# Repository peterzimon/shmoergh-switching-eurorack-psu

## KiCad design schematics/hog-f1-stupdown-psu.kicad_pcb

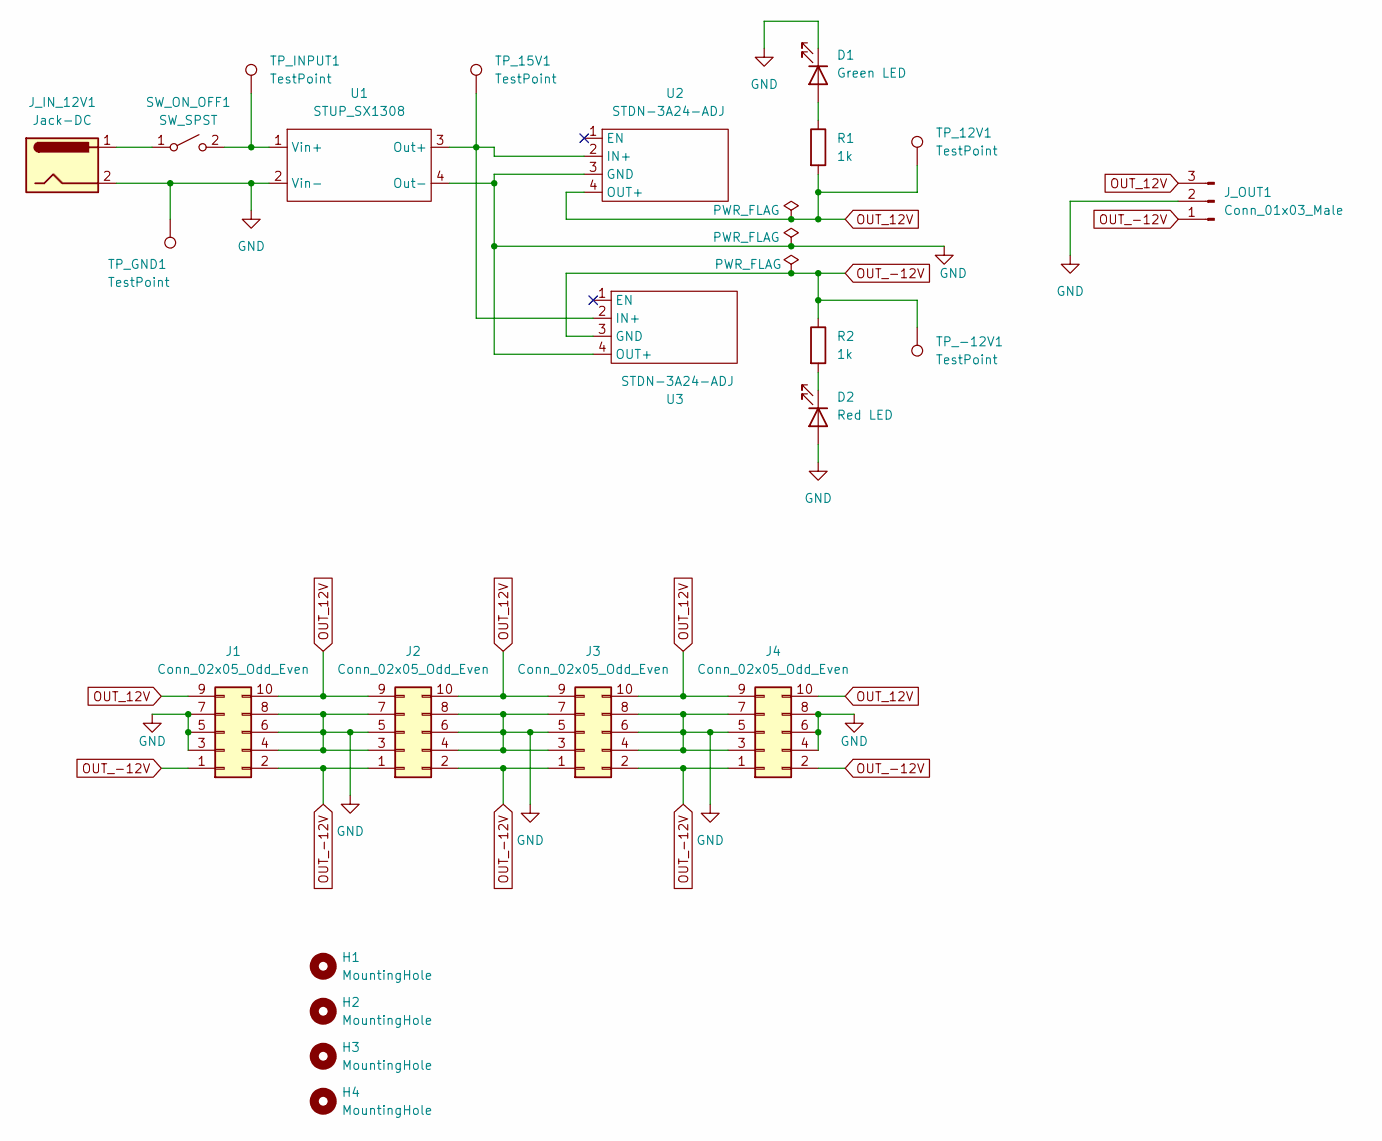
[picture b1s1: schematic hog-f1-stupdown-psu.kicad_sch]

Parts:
D1: Green LED; LED_D5.0mm
D2: Red LED; LED_D5.0mm
H1, H2, H3, H4: MountingHole; MountingHole_3mm_Pad
J1, J2, J3, J4: Conn_02x05_Odd_Even; IDC-Header_2x05_P2.54mm_Vertical
J_IN_12V1: Jack-DC; TerminalBlock_Altech_AK300-2_P5.00mm
J_OUT1: Conn_01x03_Male; TerminalBlock_Altech_AK300-3_P5.00mm
R1, R2: 1k; R_Axial_DIN0207_L6.3mm_D2.5mm_P7.62mm_Horizontal
SW_ON_OFF1: SW_SPST; NSL25_01x02_Vertical
TP_12V1, TP_15V1: TestPoint; TestPoint_THTPad_2.0x2.0mm_Drill1.0mm
TP_-12V1: TestPoint; TestPoint_THTPad_2.0x2.0mm_Drill1.0mm
TP_GND1: TestPoint; TestPoint_THTPad_2.0x2.0mm_Drill1.0mm
TP_INPUT1: TestPoint; TestPoint_THTPad_2.0x2.0mm_Drill1.0mm
U1: STUP_SX1308; STUP-SX1308
U2, U3: STDN-3A24-ADJ

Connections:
GND: D1.1 (K), D2.2 (A), J1.3, J1.4, J1.5, J1.6, J1.7, J1.8, J2.3, J2.4, J2.5, J2.6, J2.7, J2.8, J3.3, J3.4, J3.5, J3.6, J3.7, J3.8, J4.3, J4.4, J4.5, J4.6, J4.7, J4.8, J_IN_12V1.2, J_OUT1.2, TP_GND1.1, U1.2 (Vin-), U1.4 (Out-), U2.3 (GND), U3.4 (OUT+)
unnamed: D1.2 (A), R1.1
unnamed: D2.1 (K), R2.2
unnamed: J_IN_12V1.1, SW_ON_OFF1.1 (A)
unnamed: SW_ON_OFF1.2 (B), TP_INPUT1.1, U1.1 (Vin+)
unnamed: TP_15V1.1, U1.3 (Out+), U2.2 (IN+), U3.2 (IN+)
OUT_12V: J1.9, J1.10, J2.9, J2.10, J3.9, J3.10, J4.9, J4.10, J_OUT1.3, R1.2, TP_12V1.1, U2.4 (OUT+)
OUT_-12V: J1.1, J1.2, J2.1, J2.2, J3.1, J3.2, J4.1, J4.2, J_OUT1.1, R2.1, TP_-12V1.1, U3.3 (GND)

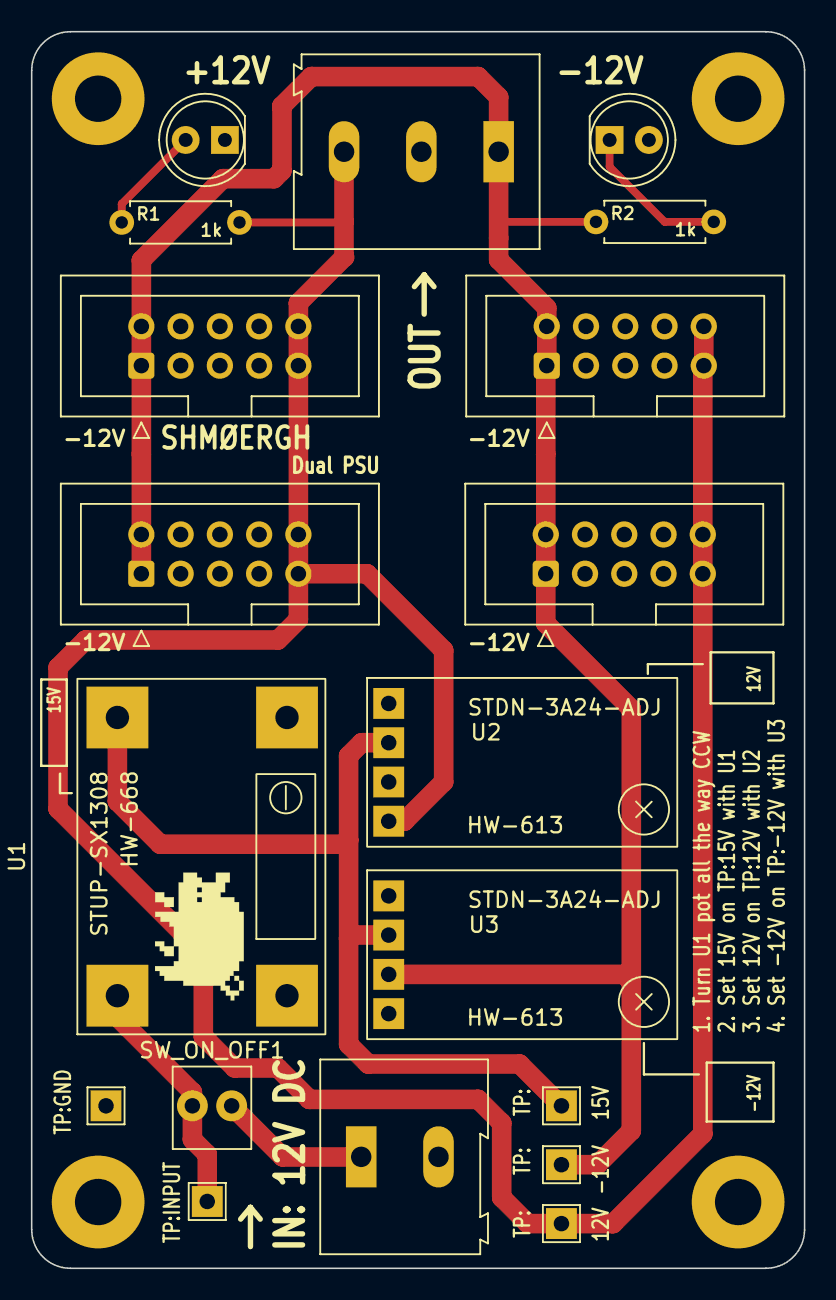
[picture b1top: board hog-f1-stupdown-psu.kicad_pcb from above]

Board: 2 copper layers, 50.0 x 80.0 mm, 23 parts (0 on the bottom side), 8 nets.
